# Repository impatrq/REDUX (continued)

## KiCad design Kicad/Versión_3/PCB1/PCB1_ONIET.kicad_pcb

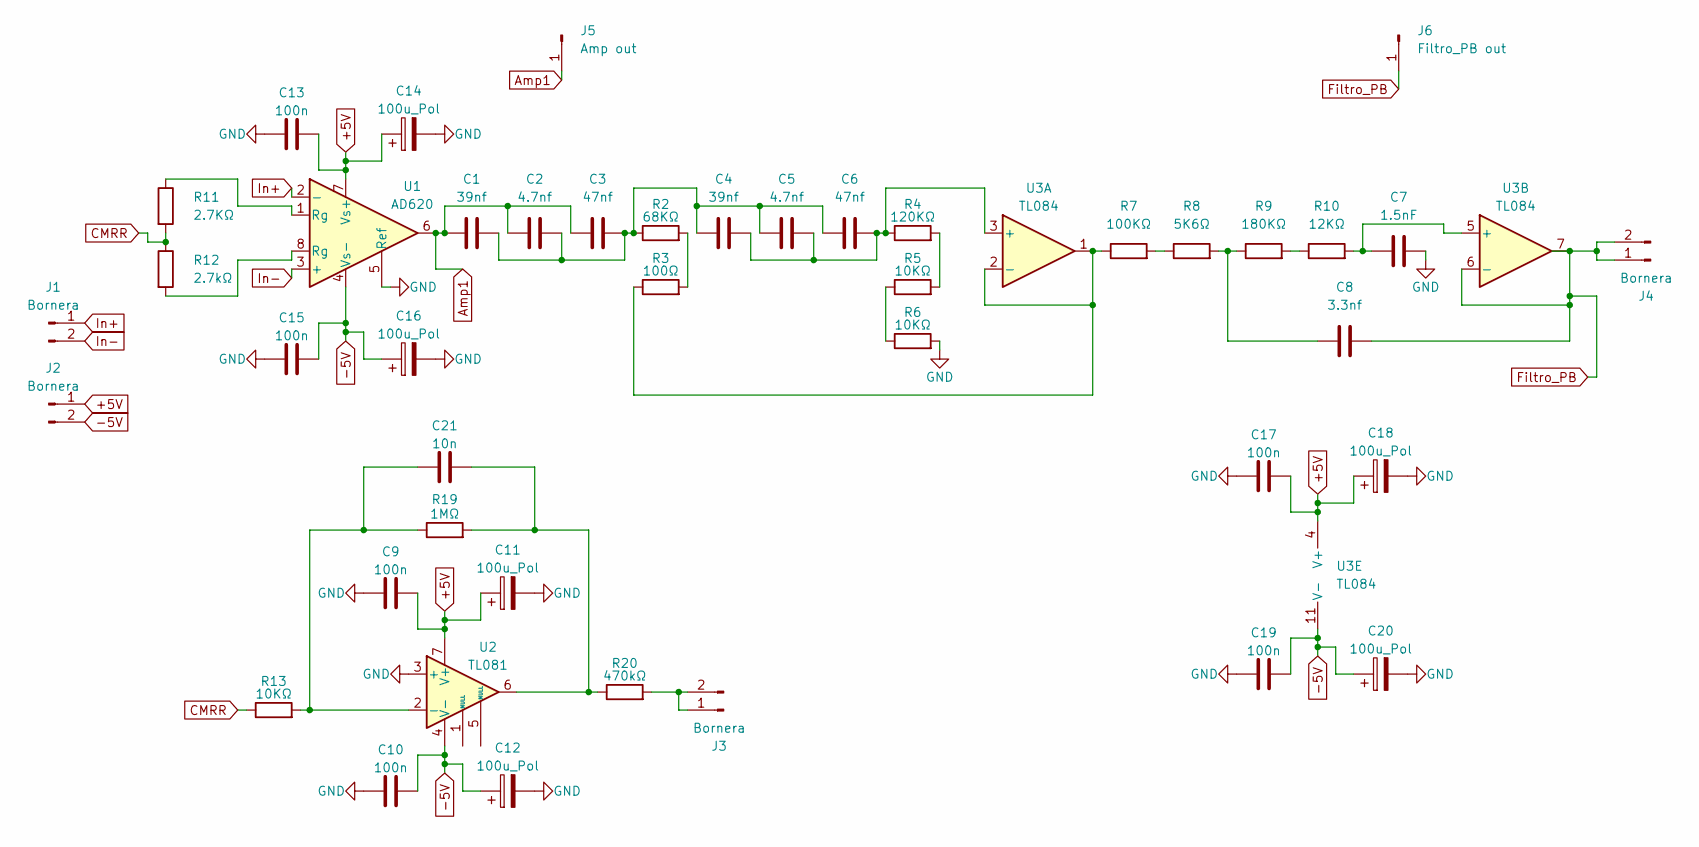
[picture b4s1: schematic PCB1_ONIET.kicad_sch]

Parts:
C1, C4: 39nf; C_Disc_D10.5mm_W5.0mm_P10.00mm
C2, C5: 4.7nf; C_Disc_D10.5mm_W5.0mm_P10.00mm
C3, C6: 47nf; C_Disc_D10.5mm_W5.0mm_P10.00mm
C7: 1.5nF; C_Disc_D10.5mm_W5.0mm_P10.00mm
C8: 3.3nf; C_Disc_D10.5mm_W5.0mm_P10.00mm
C9, C10, C13, C15, C17, C19: 100n; C_Disc_D10.5mm_W5.0mm_P10.00mm
C11, C12, C14, C16, C18, C20: 100u_Pol; C_Radial_D5.0mm_H11.0mm_P2.00mm
C21: 10n; C_Disc_D10.5mm_W5.0mm_P10.00mm
J1, J2, J3, J4: Bornera; TerminalBlock_MetzConnect_Type011_RT05502HBLC_1x02_P5.00mm_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
J5: Amp out; PinHeader_1x01_P2.00mm_Vertical
J6: Filtro_PB out; PinHeader_1x01_P2.00mm_Vertical
R2: 68KΩ; R_Axial_DIN0207_L6.3mm_D2.5mm_P10.16mm_Horizontal
R3: 100Ω; R_Axial_DIN0207_L6.3mm_D2.5mm_P10.16mm_Horizontal
R4: 120KΩ; R_Axial_DIN0207_L6.3mm_D2.5mm_P10.16mm_Horizontal
R5, R6, R13: 10KΩ; R_Axial_DIN0207_L6.3mm_D2.5mm_P10.16mm_Horizontal
R7: 100KΩ; R_Axial_DIN0207_L6.3mm_D2.5mm_P10.16mm_Horizontal
R8: 5K6Ω; R_Axial_DIN0207_L6.3mm_D2.5mm_P10.16mm_Horizontal
R9: 180KΩ; R_Axial_DIN0207_L6.3mm_D2.5mm_P10.16mm_Horizontal
R10: 12KΩ; R_Axial_DIN0207_L6.3mm_D2.5mm_P10.16mm_Horizontal
R11: 2.7KΩ; R_Axial_DIN0207_L6.3mm_D2.5mm_P10.16mm_Horizontal
R12: 2.7kΩ; R_Axial_DIN0207_L6.3mm_D2.5mm_P10.16mm_Horizontal
R19: 1MΩ; R_Axial_DIN0207_L6.3mm_D2.5mm_P10.16mm_Horizontal
R20: 470kΩ; R_Axial_DIN0207_L6.3mm_D2.5mm_P10.16mm_Horizontal
U1: AD620; DIP-8_W7.62mm
U2: TL081; DIP-8_W7.62mm_LongPads
U3: TL084; DIP-14_W7.62mm_LongPads

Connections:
+5V: C9.2, C11.1, C13.2, C14.1, C17.2, C18.1, J2.1, U1.7 (Vs+), U2.7 (V+), U3.4 (V+)
-5V: C10.2, C12.1, C15.2, C16.1, C19.2, C20.1, J2.2, U1.4 (Vs-), U2.4 (V-), U3.11 (V-)
Amp1: C1.1, C2.1, C3.1, J5.1 (Pin_1_1), U1.6
CMRR: R11.2, R12.1, R13.1
Filtro_PB: C8.2, J4.1, J4.2, J6.1 (Pin_1_1), U3.6 (-), U3.7
GND: C7.2, C9.1, C10.1, C11.2, C12.2, C13.1, C14.2, C15.1, C16.2, C17.1, C18.2, C19.1, C20.2, R6.2, U1.5 (Ref), U2.3 (+)
In+: J1.1, U1.2 (-)
In-: J1.2, U1.3 (+)
unnamed: C1.2, C2.2, C3.2, C4.1, C5.1, C6.1, R2.1
unnamed: C8.1, R8.2, R9.1
unnamed: C21.2, R19.2, R20.1, U2.6
unnamed: J3.1, J3.2, R20.2
unnamed: R2.2, R3.2
unnamed: R4.2, R5.2
unnamed: R5.1, R6.1
unnamed: R7.2, R8.1
unnamed: R9.2, R10.1
unnamed: R11.1, U1.1 (Rg)
unnamed: R12.2, U1.8 (Rg)
unnamed: C21.1, R13.2, R19.1, U2.2 (-)
unnamed: C4.2, C5.2, C6.2, R4.1, U3.3 (+)
unnamed: R3.1, R7.1, U3.1, U3.2 (-)
unnamed: C7.1, R10.2, U3.5 (+)

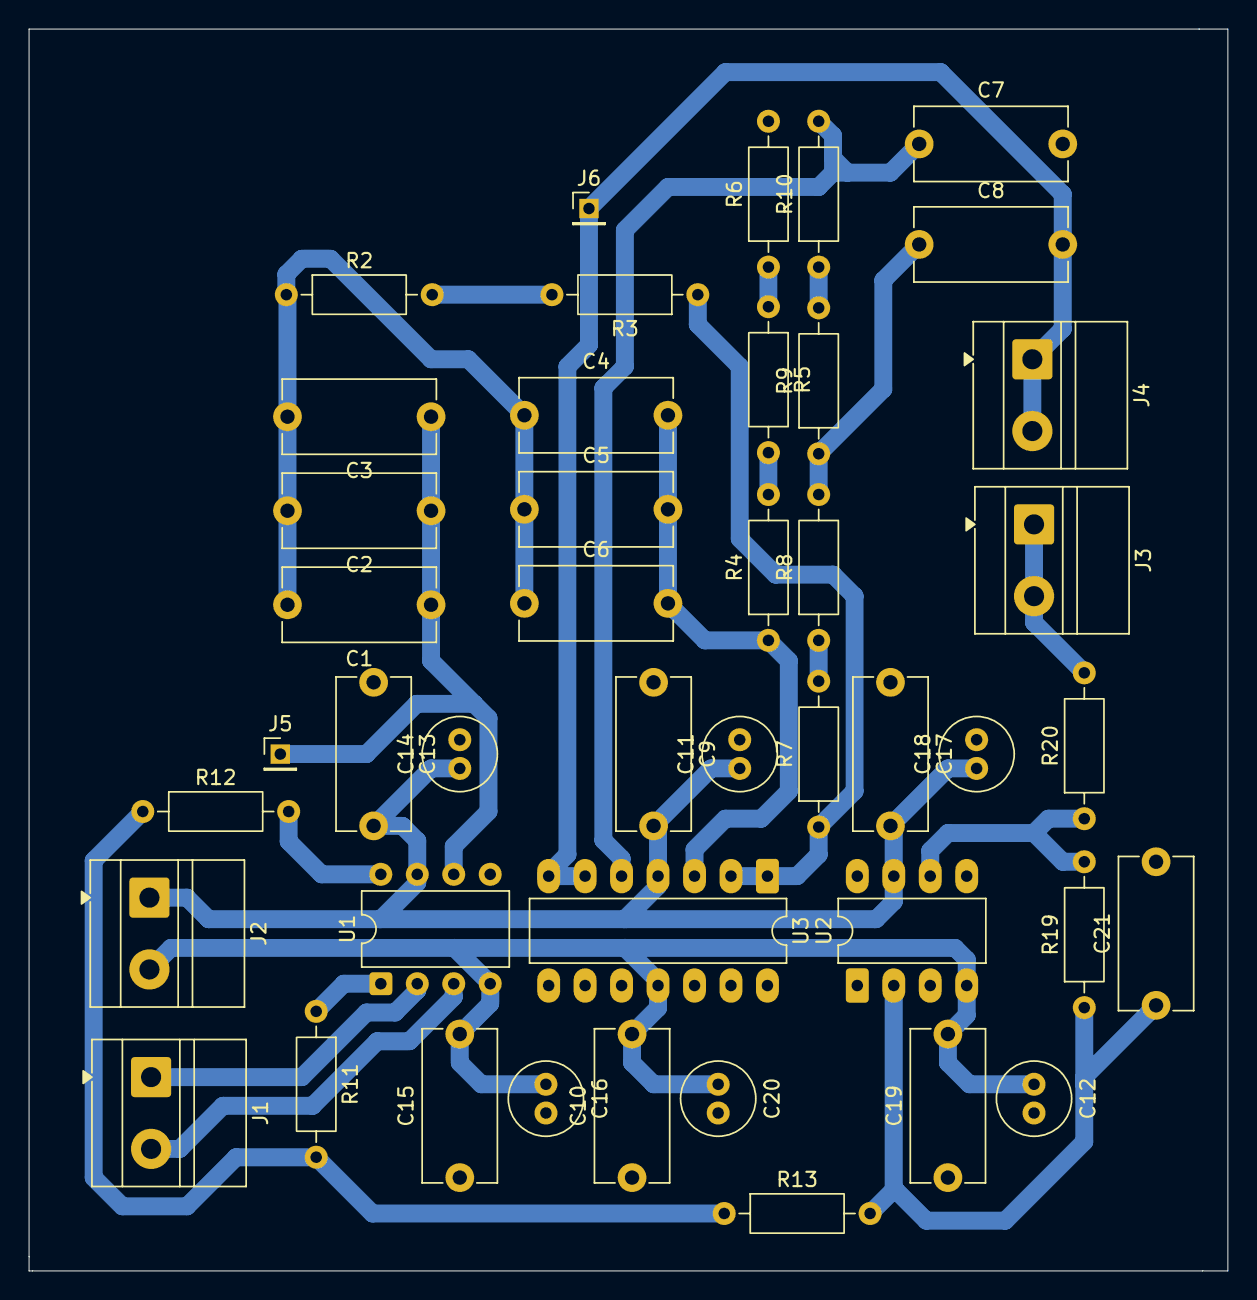
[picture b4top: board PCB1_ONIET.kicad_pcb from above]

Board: 2 copper layers, 83.5 x 86.5 mm, 44 parts (0 on the bottom side), 23 nets.

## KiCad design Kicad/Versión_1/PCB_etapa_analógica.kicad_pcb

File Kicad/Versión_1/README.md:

Primer diseño de kicad de la amplificación y los filtros para sEMG.

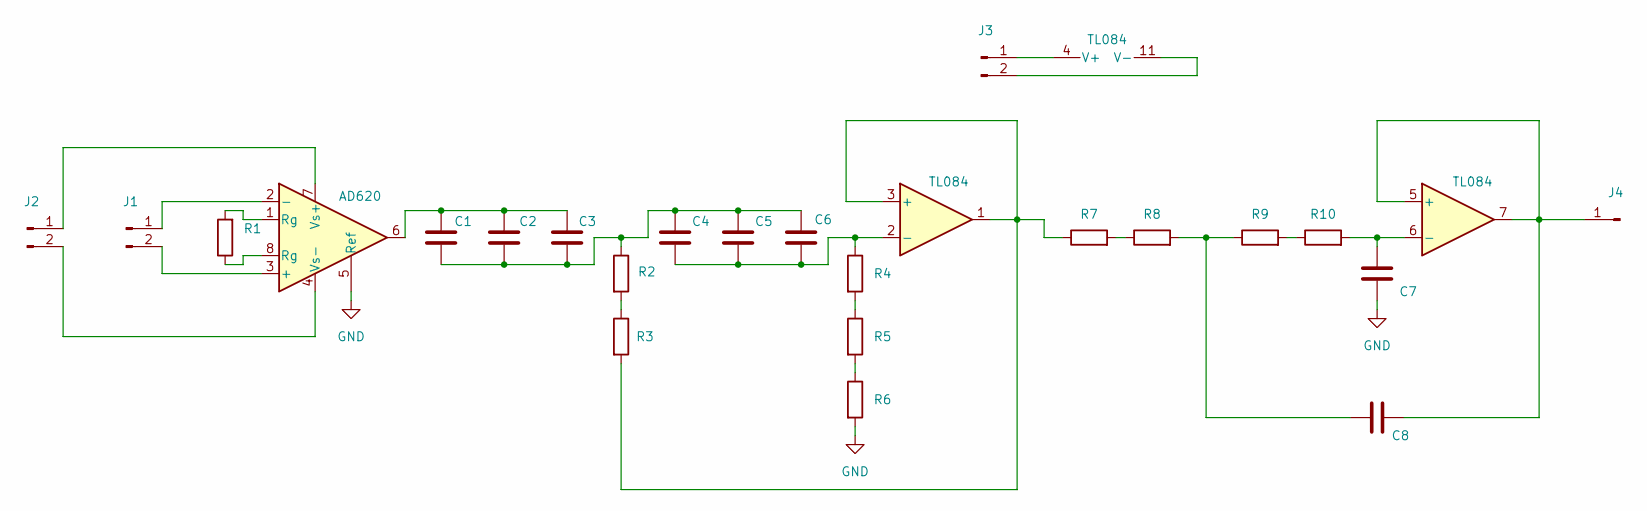
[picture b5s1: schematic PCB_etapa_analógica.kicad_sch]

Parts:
C1, C2, C3, C4, C5, C6, C7, C8: C; C_Disc_D6.0mm_W2.5mm_P5.00mm
J1, J2, J3: Conn_01x02_Pin; PinHeader_1x02_P2.00mm_Vertical
J4: Conn_01x01_Pin; PinHeader_1x01_P2.00mm_Vertical
R1, R2, R3, R4, R5, R6, R7, R8, R9, R10: R; R_Axial_DIN0207_L6.3mm_D2.5mm_P10.16mm_Horizontal
U1: AD620; DIP-8_W7.62mm
U2: TL084; DIP-14_W7.62mm_LongPads

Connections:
GND: C7.2, R6.2, U1.5 (Ref)
unnamed: C1.1, C2.2, C3.2, C4.2, C5.2, C6.2, R2.1
unnamed: C1.2, C2.1, C3.1, U1.6
unnamed: C8.2, R8.2, R9.1
unnamed: J1.1, U1.2 (-)
unnamed: J1.2, U1.3 (+)
unnamed: J2.1, U1.7 (Vs+)
unnamed: J2.2, U1.4 (Vs-)
unnamed: J3.1, U2.4 (V+)
unnamed: J3.2, U2.11 (V-)
unnamed: C8.1, J4.1 (Pin_1_1), U2.5 (+), U2.7
unnamed: R1.1, U1.8 (Rg)
unnamed: R1.2, U1.1 (Rg)
unnamed: R2.2, R3.1
unnamed: R4.2, R5.1
unnamed: R5.2, R6.1
unnamed: R7.2, R8.1
unnamed: R9.2, R10.1
unnamed: R3.2, R7.1, U2.1, U2.3 (+)
unnamed: C4.1, C5.1, C6.1, R4.1, U2.2 (-)
unnamed: C7.1, R10.2, U2.6 (-)

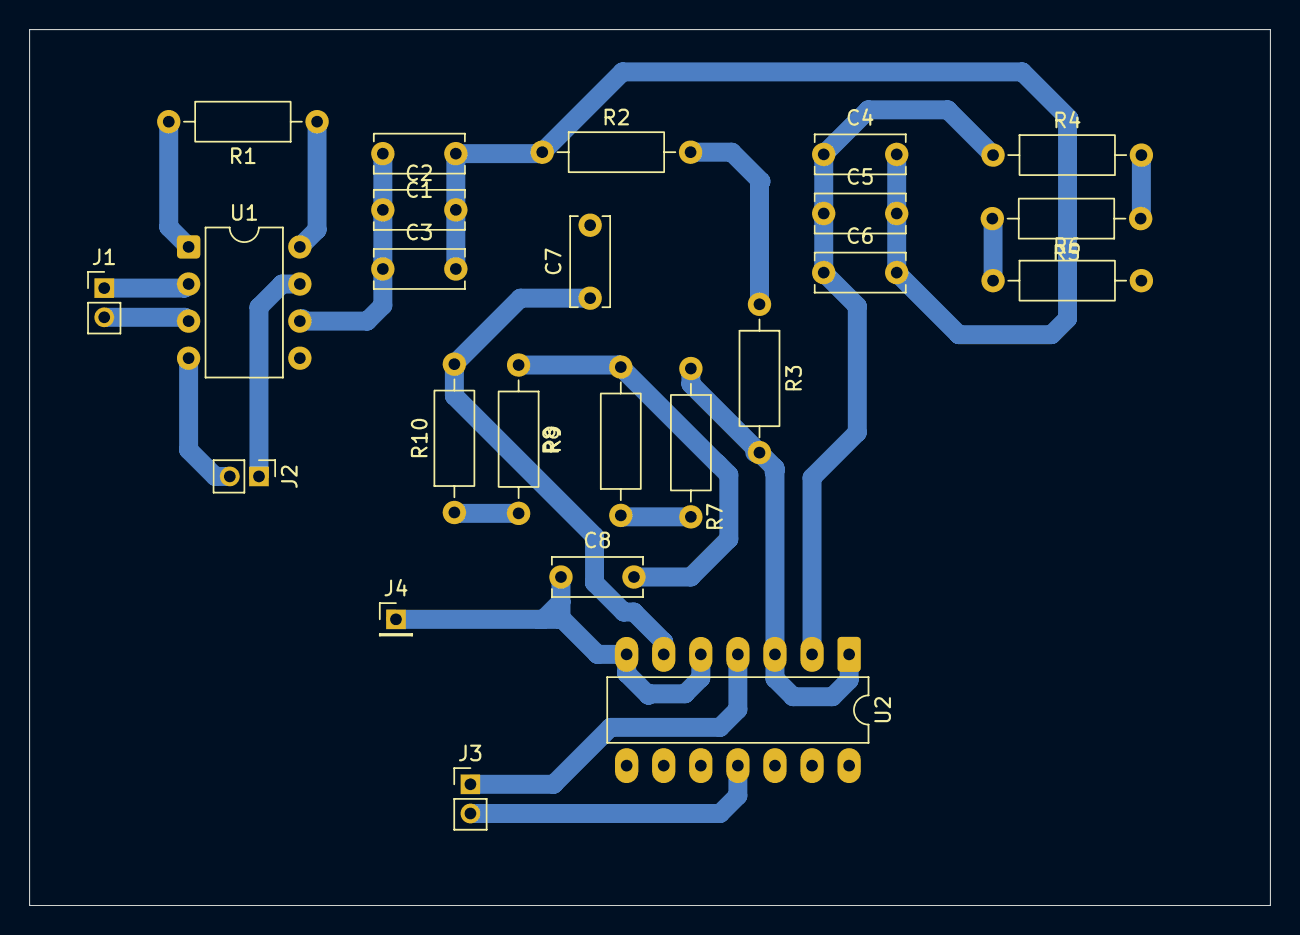
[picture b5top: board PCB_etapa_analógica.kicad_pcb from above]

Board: 2 copper layers, 85.0 x 60.0 mm, 24 parts (0 on the bottom side), 21 nets.

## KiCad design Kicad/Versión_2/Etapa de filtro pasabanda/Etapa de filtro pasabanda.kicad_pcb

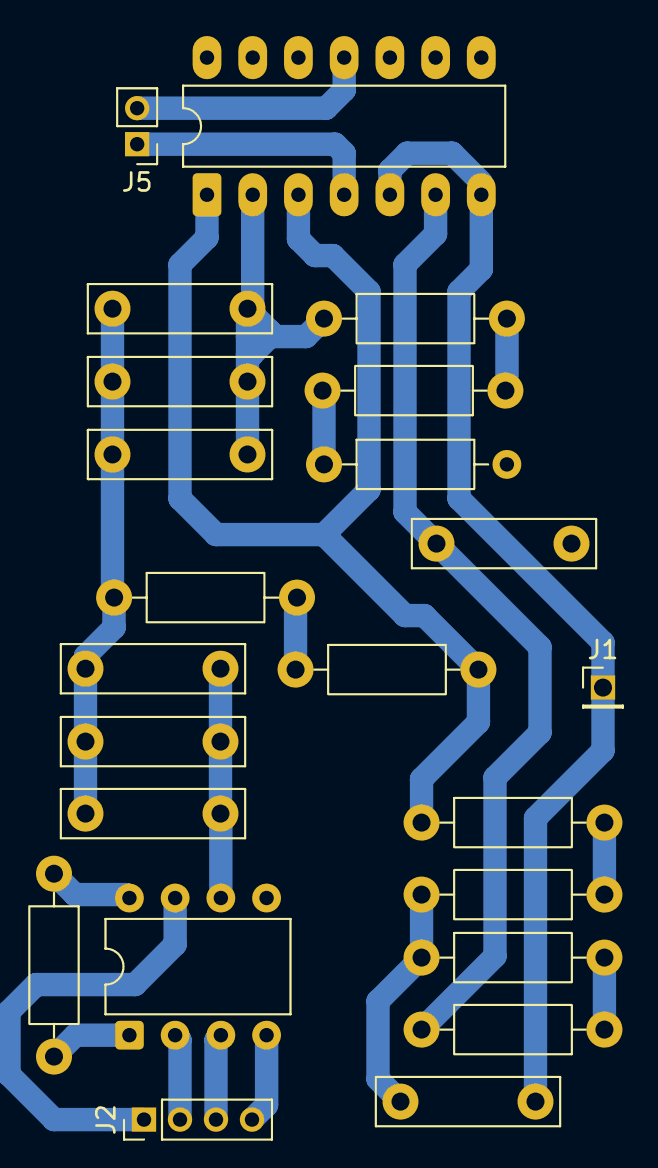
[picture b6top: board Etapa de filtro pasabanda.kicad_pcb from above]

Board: 2 copper layers, 23 parts (0 on the bottom side), 21 nets.

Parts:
1.5nF, 3.3nF, 4.7nF, 4.7nF#2, 39nF, 39nF#2, 47nF#2: C; C_Rect_L10.0mm_W2.5mm_P7.50mm_MKS4
5.6kΩ, 10kΩ, 10kΩ#2, 12kΩ, 68kΩ, 100kΩ, 100Ω, 120kΩ, 180kΩ, 470Ω: R; R_Axial_DIN0207_L6.3mm_D2.5mm_P10.16mm_Horizontal
47nF: 47nf; C_Rect_L10.0mm_W2.5mm_P7.50mm_MKS4
J1: Conn_01x01_Pin; PinHeader_1x01_P2.00mm_Vertical
J2: Conn_01x04_Pin; PinHeader_1x04_P2.00mm_Vertical
J5: Conn_01x02_Pin; PinHeader_1x02_P2.00mm_Vertical
U1: AD620; DIP-8_W7.62mm
U2: TL084; DIP-14_W7.62mm_LongPads

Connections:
GND: 1.5nF.2, 10kΩ.2, U1.5 (Ref)
unnamed: 4.7nF.2, 4.7nF#2.2, 39nF.2, 39nF#2.2, 47nF.1, 47nF#2.2, 68kΩ.1
unnamed: 4.7nF#2.1, 39nF.1, 47nF.2, U1.6
unnamed: 3.3nF.2, 5.6kΩ.2, 180kΩ.1
unnamed: 3.3nF.1, J1.1 (Pin_1_1), U2.5 (+), U2.7
unnamed: J2.1, U1.7 (Vs+)
unnamed: J2.2, U1.2 (-)
unnamed: J2.3, U1.3 (+)
unnamed: J2.4, U1.4 (Vs-)
unnamed: J5.1, U2.4 (V+)
unnamed: J5.2, U2.11 (V-)
unnamed: 470Ω.1, U1.8 (Rg)
unnamed: 470Ω.2, U1.1 (Rg)
unnamed: 68kΩ.2, 100Ω.1
unnamed: 10kΩ#2.1, 120kΩ.2
unnamed: 10kΩ.1, 10kΩ#2.2
unnamed: 5.6kΩ.1, 100kΩ.2
unnamed: 12kΩ.1, 180kΩ.2
unnamed: 100kΩ.1, 100Ω.2, U2.1, U2.3 (+)
unnamed: 4.7nF.1, 39nF#2.1, 47nF#2.1, 120kΩ.1, U2.2 (-)
unnamed: 1.5nF.1, 12kΩ.2, U2.6 (-)

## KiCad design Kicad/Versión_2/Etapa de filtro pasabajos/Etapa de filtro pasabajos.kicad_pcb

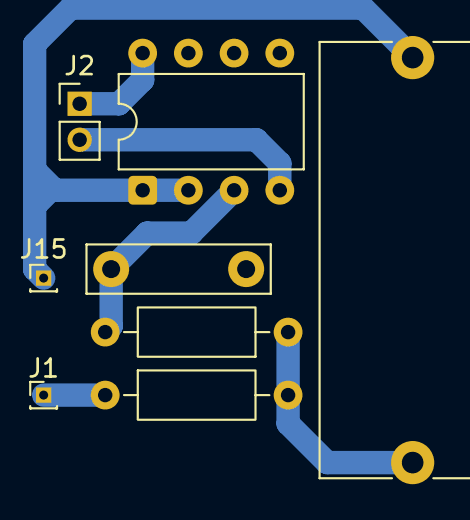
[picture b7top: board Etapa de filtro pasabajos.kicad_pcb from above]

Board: 2 copper layers, 8 parts (0 on the bottom side), 6 nets.

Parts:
1.5uF: C; C_Rect_L24.0mm_W10.1mm_P22.50mm_MKT
33kΩ, 33kΩ#2: R; R_Axial_DIN0207_L6.3mm_D2.5mm_P10.16mm_Horizontal
680nF: C; C_Rect_L10.0mm_W2.5mm_P7.50mm_MKS4
J1, J15: Conn_01x01_Pin; PinHeader_1x01_P1.00mm_Vertical
J2: Conn_01x02_Pin; PinHeader_1x02_P2.00mm_Vertical
U5: TL082; DIP-8_W7.62mm

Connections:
unnamed: 1.5uF.1, 33kΩ.1, 33kΩ#2.2
unnamed: 33kΩ#2.1, J1.1 (Pin_1_1)
unnamed: J2.1, U5.8 (V+)
unnamed: J2.2, U5.4 (V-)
unnamed: 1.5uF.2, J15.1 (Pin_1_1), U5.1, U5.2 (-)
unnamed: 33kΩ.2, 680nF.1, U5.3 (+)

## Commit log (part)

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2026-04-08 Se agrega el anteproyecto
2026-04-10 Se agrega la carpeta de Documentos
2026-04-14 fix Anteproyecto.pdf
2026-04-17 Simulación experimental filtros
2026-05-20 Feat: añado código fuente de pagina web
2026-05-20 Feat: agrego a la pagina web la pagina de contacto
2026-05-20 Docs/GS/Añado pruebas sobre el progresa sobre la estructura del proyecto.
2026-05-26 feat(circuitos): agregar diseños de filtros EMG pasa banda
    Se añaden los archivos de simulación de LTSpice (.asc) y las capturas de pantalla de estos mismos
2026-05-27 Feat: Agrego primera prueba de comunicacion
2026-05-27 feat: agregar diseño kicad filtros
2026-06-05 feat: Agrego prueba preliminar de la API
2026-06-10 fix: modifico esquemático corregido
2026-06-10 docs:justificacion-seguridad-medica/electrica
